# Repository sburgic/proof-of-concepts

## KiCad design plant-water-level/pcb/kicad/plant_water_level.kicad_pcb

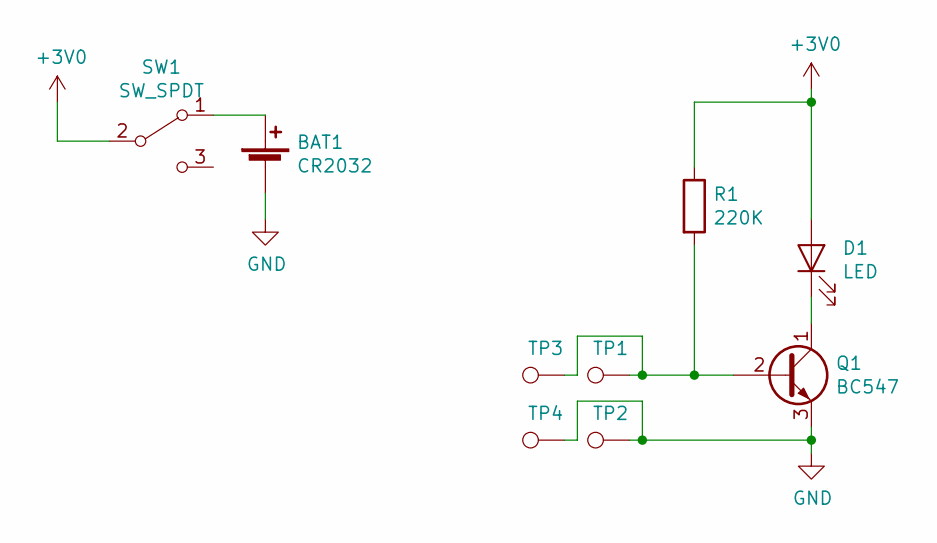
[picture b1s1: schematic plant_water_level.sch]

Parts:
BAT1: CR2032; BatteryHolder_Keystone_103_1x20mm
D1: LED; LED_D5.0mm
Q1: BC547; TO-92_Inline
R1: 220K; R_Axial_DIN0207_L6.3mm_D2.5mm_P10.16mm_Horizontal
SW1: SW_SPDT; SW_SPDT_PCM12
TP1, TP3, TP4: Probe2; TestPoint_THTPad_4.0x4.0mm_Drill2.0mm
TP2: Probe1; TestPoint_THTPad_4.0x4.0mm_Drill2.0mm

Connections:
+3V0: D1.2 (A), R1.1, SW1.2 (B)
GND: BAT1.2 (-), Q1.3 (E), TP2.1, TP4.1
unnamed: BAT1.1 (+), SW1.1 (A)
unnamed: D1.1 (K), Q1.1 (C)
unnamed: Q1.2 (B), R1.2, TP1.1, TP3.1

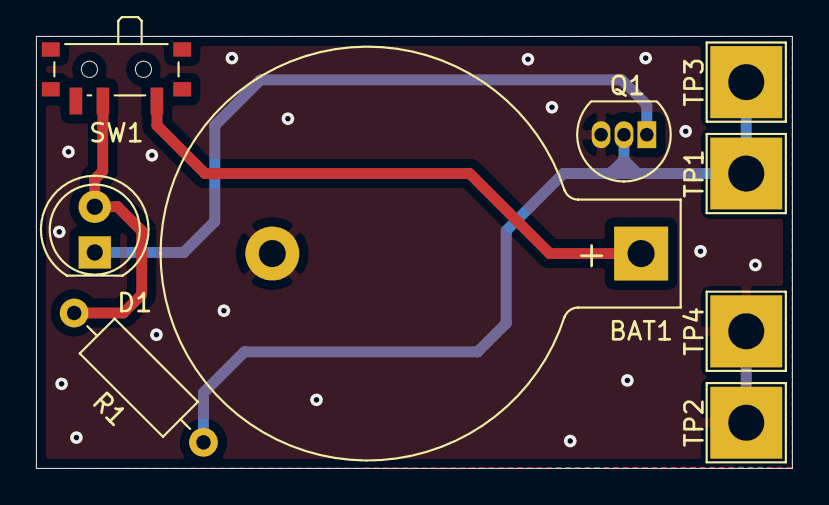
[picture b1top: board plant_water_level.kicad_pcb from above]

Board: 2 copper layers, 42.0 x 24.0 mm, 9 parts (0 on the bottom side), 5 nets.

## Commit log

2023-03-21 Add initial projects
